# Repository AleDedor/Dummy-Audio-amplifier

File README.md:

# Dummy-Audio-amplifier
A very basic, 2-stages, audio amplifier, designed with discrete THT components. 
The goal of the project is to build from scratch a simple audio amplifier in order to get familiarity with the main issues of the audio world.

## Main concerns:

- **Noise level**, keep it as low as possible adding decoupling capacitor as close as possible to the LM741 amplifiers (switching noise of the DCDC converter) and using low value resistors (Thermal noise).
- **Limited Bandwidth**, in order to reduce noise r.m.s. and filter out external disturbs.
- **Push-pull final stage thermal runaway**, biasing BJTs with fixed base-emitter voltage cause high dependance on temperature. Introduce emitter resistance to counteract.
- Compensate for Loudspeaker increasing impedance over audio bandwidth with a **Zobel network**.
- Avoid **loop instability** (output stage).

## Soldered PCB image:

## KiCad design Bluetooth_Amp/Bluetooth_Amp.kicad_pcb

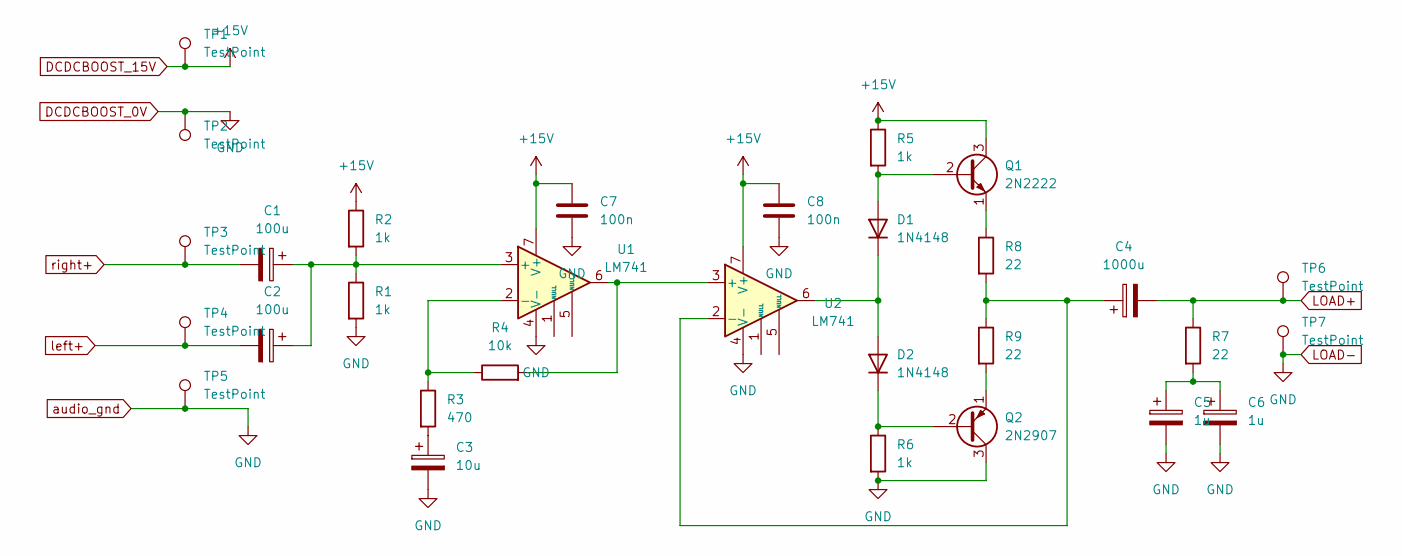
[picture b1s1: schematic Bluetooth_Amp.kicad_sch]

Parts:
C1, C2: 100u; CP_Radial_D6.3mm_P2.50mm
C3: 10u; CP_Radial_D4.0mm_P2.00mm
C4: 1000u; CP_Radial_D10.0mm_P5.00mm
C5: 1u; CP_Radial_D4.0mm_P2.00mm
C6: 1u; CP_Radial_D4.0mm_P1.50mm
C7, C8: 100n; C_Rect_L7.0mm_W2.5mm_P5.00mm
D1, D2: 1N4148; D_DO-35_SOD27_P7.62mm_Horizontal
Q1: 2N2222; TO-18-3
Q2: 2N2907; TO-18-3
R1, R2, R5, R6: 1k; R_Axial_DIN0207_L6.3mm_D2.5mm_P10.16mm_Horizontal
R3: 470; R_Axial_DIN0207_L6.3mm_D2.5mm_P10.16mm_Horizontal
R4: 10k; R_Axial_DIN0207_L6.3mm_D2.5mm_P10.16mm_Horizontal
R7, R8, R9: 22; R_Axial_DIN0207_L6.3mm_D2.5mm_P10.16mm_Horizontal
TP1, TP2, TP3, TP4, TP5, TP6, TP7: TestPoint; TestPoint_Pad_2.5x2.5mm
U1, U2: LM741; DIP-8_W7.62mm_LongPads

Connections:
DCDCBOOST_0V: C3.2, C5.2, C6.2, C7.2, C8.2, Q2.3 (C), R1.2, R6.2, TP2.1, TP5.1, TP7.1, U1.4 (V-), U2.4 (V-)
DCDCBOOST_15V: C7.1, C8.1, Q1.3 (C), R2.1, R5.1, TP1.1, U1.7 (V+), U2.7 (V+)
LOAD+: C4.2, R7.1, TP6.1
unnamed: C1.1, C2.1, R1.1, R2.2, U1.3 (+)
unnamed: C3.1, R3.2
unnamed: C4.1, R8.2, R9.1, U2.2 (-)
unnamed: C5.1, C6.1, R7.2
unnamed: D1.1 (K), D2.2 (A), U2.6
unnamed: D1.2 (A), Q1.2 (B), R5.2
unnamed: D2.1 (K), Q2.2 (B), R6.1
unnamed: Q1.1 (E), R8.1
unnamed: Q2.1 (E), R9.2
unnamed: R3.1, R4.1, U1.2 (-)
unnamed: R4.2, U1.6, U2.3 (+)
left+: C2.2, TP4.1
right+: C1.2, TP3.1

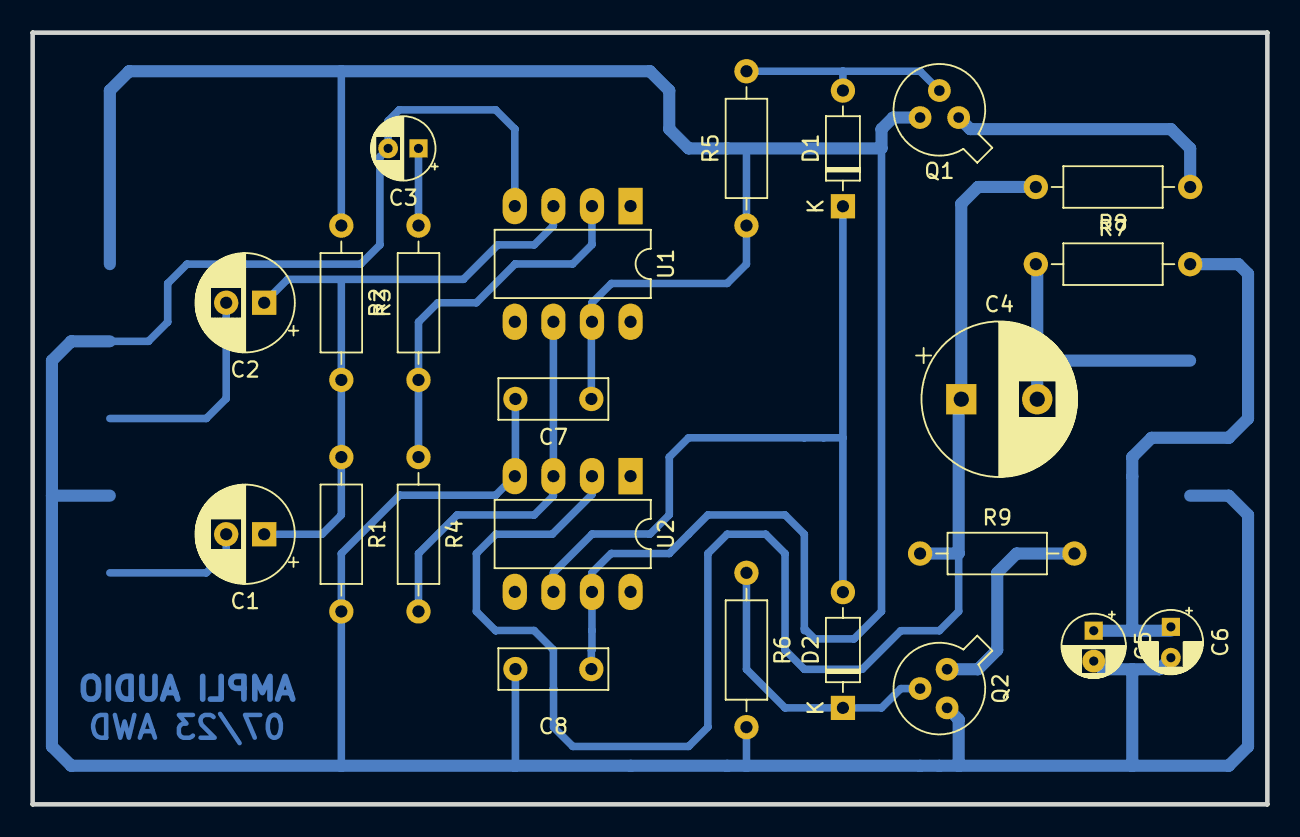
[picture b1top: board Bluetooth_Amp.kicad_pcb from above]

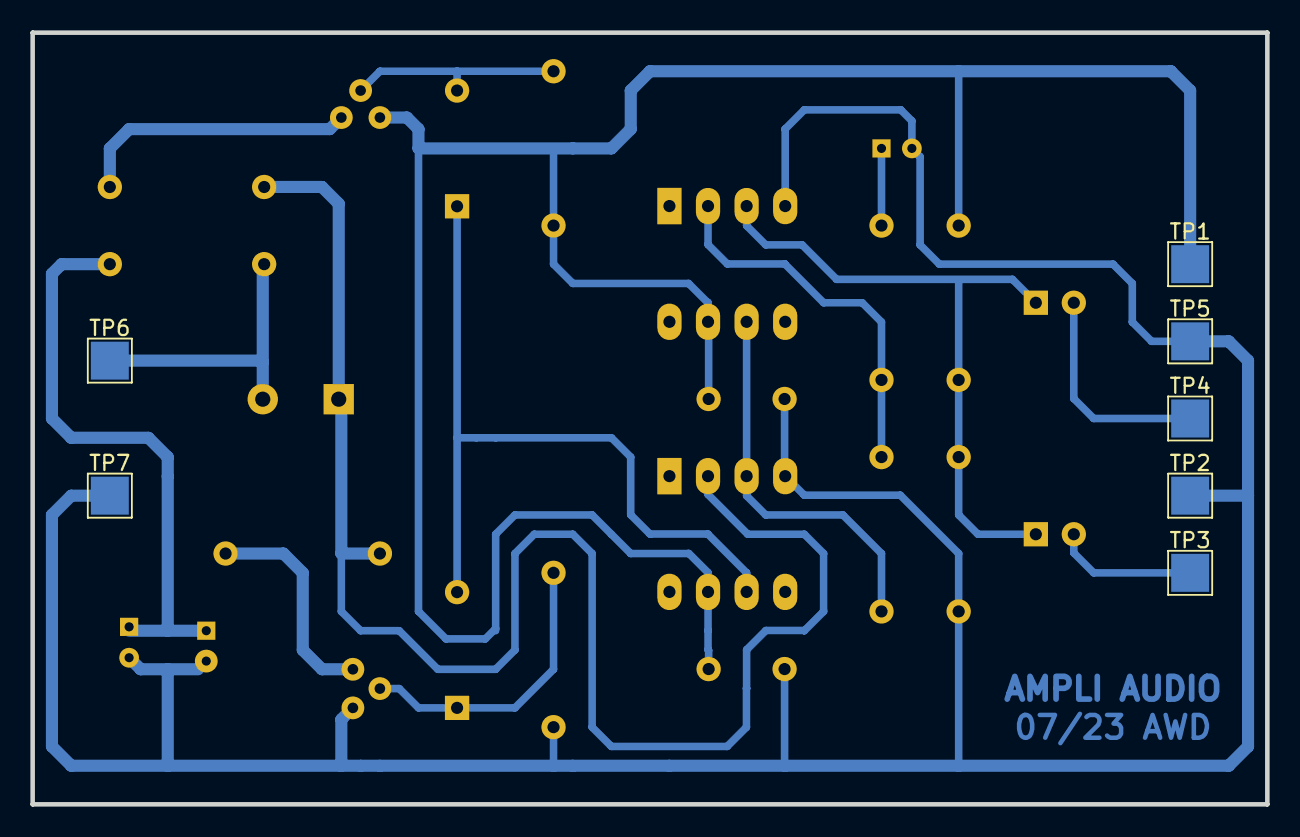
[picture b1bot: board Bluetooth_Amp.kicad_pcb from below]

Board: 2 copper layers, 81.3 x 50.8 mm, 30 parts (7 on the bottom side), 16 nets.

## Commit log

2024-02-29 Added all files
2024-09-03 final pcb image
